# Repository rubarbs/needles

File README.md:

Needles
is a 1U Eurorack Midi Controller and Mutable Instruments Yarns Companion.

This module was designed to take full advantage of Yarn's capabilities. Most of Yarn's menu settings can be accessed and changed directly from Needles front panel, allowing for very fast and intuitive workflow.

See the guides for more info.

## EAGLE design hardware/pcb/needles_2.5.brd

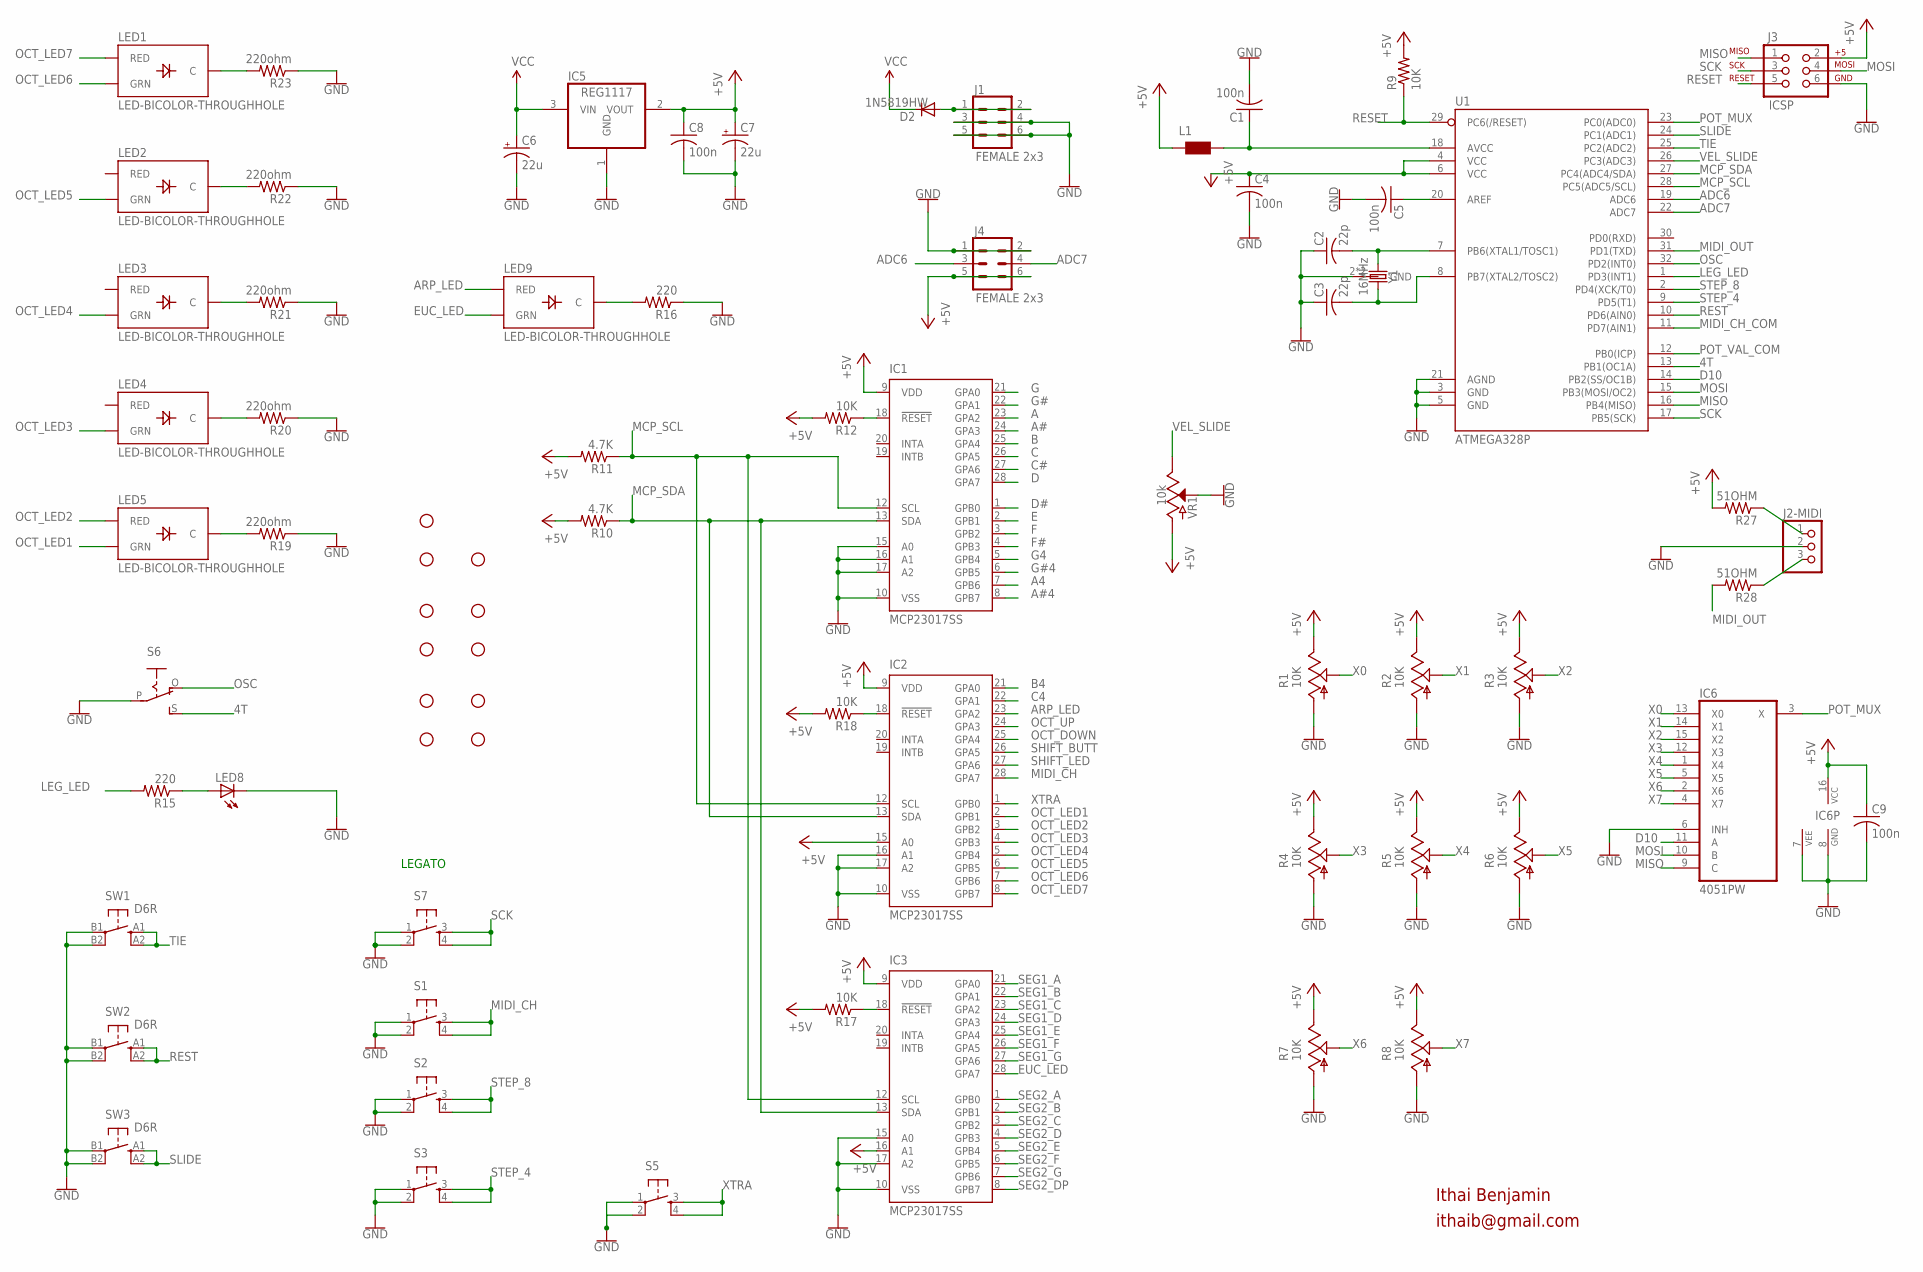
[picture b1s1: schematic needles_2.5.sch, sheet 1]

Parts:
C1, C4, C5, C8, C9: 100n; C0603
C2, C3: 22p; C0603
C6, C7: 22u; PANASONIC_C
D2: 1N5819HW; SOD123
H1, H2, H3, H4, H5, H6, H7, H8, H9, H10, H11: STAND-OFF
IC1, IC2, IC3: MCP23017SS; SSOP28
IC5: REG1117; SOT223
IC6: 4051PW; TSSOP16
J1, J4: FEMALE 2x3; 2X3
J2-MIDI: PINHD-1X3; 1X03
J3: ICSP; 2X3
L1: WE-CBF_0603; 0603
LED1, LED2, LED3, LED4, LED5, LED9: LED-BICOLOR-THROUGHHOLE
LED8: LED3MM
R1, R2, R3, R4, R5, R6, R7, R8: 10K; ALPS_POT_VERTICAL
R9, R12, R17, R18: 10K; R0603
R10, R11: 4.7K; R0603
R15, R16: 220; R0603
R19, R20, R21, R22, R23: 220ohm; R0603
R27, R28: 51OHM; R0603
S1, S2, S3, S5, S7: TAC_SWITCHPTH; TACTILE-PTH
S6: S-ON-ONSMALL_SLIDE; ES_100SP1T6B11M2QEH_SMALL
SW1, SW2, SW3: D6R
U1: ATMEGA328P; TQFP32-08
VR1: 10k; SLIDER-MEDIUM
Y1: 16MHz; CRYSTAL-SMD-5X3.2-4PAD

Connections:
4T: S6.S, U1.13 (PB1(OC1A))
+5V: C4.1, C7.+, C8.1, C9.1, IC1.9 (VDD), IC2.9 (VDD), IC2.15 (A0), IC3.9 (VDD), IC3.16 (A1), IC5.2 (VOUT), IC6.16 (VCC), J3.2, J4.5, J4.6, L1.1, R1.P$1 (E), R2.P$1 (E), R3.P$1 (E), R4.P$1 (E), R5.P$1 (E), R6.P$1 (E), R7.P$1 (E), R8.P$1 (E), R9.2, R10.2, R11.2, R12.2, R17.2, R18.2, R27.2, U1.4 (VCC), U1.6 (VCC), VR1.BOTTOM (A); also elsewhere on the board
A: IC1.23 (GPA2); also elsewhere on the board
A4: IC1.7 (GPB6); also elsewhere on the board
A#: IC1.24 (GPA3); also elsewhere on the board
A#4: IC1.8 (GPB7); also elsewhere on the board
ADC6: J4.3, U1.19 (ADC6)
ADC7: J4.4, U1.22 (ADC7)
AREF: C5.1, U1.20 (AREF)
ARP_LED: IC2.23 (GPA2), LED9.3 (RED)
B: IC1.25 (GPA4); also elsewhere on the board
B4: IC2.21 (GPA0); also elsewhere on the board
C: IC1.26 (GPA5); also elsewhere on the board
C4: IC2.22 (GPA1); also elsewhere on the board
C#: IC1.27 (GPA6); also elsewhere on the board
D: IC1.28 (GPA7); also elsewhere on the board
D10: IC6.11 (A), U1.14 (PB2(SS/OC1B))
D#: IC1.1 (GPB0); also elsewhere on the board
E: IC1.2 (GPB1); also elsewhere on the board
EUC_LED: IC3.28 (GPA7), LED9.1 (GRN)
F: IC1.3 (GPB2); also elsewhere on the board
F#: IC1.4 (GPB3); also elsewhere on the board
G: IC1.21 (GPA0); also elsewhere on the board
G4: IC1.5 (GPB4); also elsewhere on the board
G#: IC1.22 (GPA1); also elsewhere on the board
G#4: IC1.6 (GPB5); also elsewhere on the board
GND: C1.2, C2.1, C3.1, C4.2, C5.2, C6.-, C7.-, C8.2, C9.2, IC1.10 (VSS), IC1.15 (A0), IC1.16 (A1), IC1.17 (A2), IC2.10 (VSS), IC2.16 (A1), IC2.17 (A2), IC3.10 (VSS), IC3.15 (A0), IC3.17 (A2), IC5.1 (GND), IC6.6 (INH), IC6.7 (VEE), IC6.8 (GND), J1.3, J1.4, J1.5, J1.6, J2-MIDI.2, J3.6, J4.1, J4.2, LED8.K (C), R1.P$3 (A), R2.P$3 (A), R3.P$3 (A), R4.P$3 (A), R5.P$3 (A), R6.P$3 (A), R7.P$3 (A), R8.P$3 (A), R16.1, R19.1, R20.1, R21.1, R22.1, R23.1, S1.1, S1.2, S2.1, S2.2, S3.1, S3.2, S5.1, S5.2, S6.P, S7.1, S7.2, SW1.B1, SW1.B2 (P1), SW2.B1, SW2.B2 (P1), SW3.B1, SW3.B2 (P1), U1.3 (GND), U1.5 (GND), U1.21 (AGND), VR1.WIPER (S), Y1.2 (GND), Y1.4 (GND); also elsewhere on the board
LEG_LED: R15.2, U1.1 (PD3(INT1))
MCP_SCL: IC1.12 (SCL), IC2.12 (SCL), IC3.12 (SCL), R11.1, U1.28 (PC5(ADC5/SCL))
MCP_SDA: IC1.13 (SDA), IC2.13 (SDA), IC3.13 (SDA), R10.1, U1.27 (PC4(ADC4/SDA))
MIDI_CH: IC2.28 (GPA7), S1.3, S1.4
MIDI_CH_COM: U1.11 (PD7(AIN1)); also elsewhere on the board
MIDI_OUT: R28.2, U1.31 (PD1(TXD))
MISO: IC6.9 (C), J3.1, U1.16 (PB4(MISO))
MOSI: IC6.10 (B), J3.4, U1.15 (PB3(MOSI/OC2))
unnamed: IC1.18 (!RESET), R12.1
unnamed: IC2.18 (!RESET), R18.1
unnamed: C1.1, L1.2, U1.18 (AVCC)
unnamed: LED1.2 (C), R23.2
unnamed: C2.2, U1.7 (PB6(XTAL1/TOSC1)), Y1.1
unnamed: C3.2, U1.8 (PB7(XTAL2/TOSC2)), Y1.3 (2)
unnamed: LED2.2 (C), R22.2
unnamed: IC3.18 (!RESET), R17.1
unnamed: LED3.2 (C), R21.2
unnamed: LED4.2 (C), R20.2
unnamed: LED5.2 (C), R19.2
unnamed: J2-MIDI.1, R27.1
unnamed: J2-MIDI.3, R28.1
unnamed: LED8.A, R15.1
unnamed: LED9.2 (C), R16.2
unnamed: D2.A, J1.1, J1.2
OCT_DOWN: IC2.25 (GPA4); also elsewhere on the board
OCT_LED1: IC2.2 (GPB1), LED5.1 (GRN)
OCT_LED2: IC2.3 (GPB2), LED5.3 (RED)
OCT_LED3: IC2.4 (GPB3), LED4.1 (GRN)
OCT_LED4: IC2.5 (GPB4), LED3.1 (GRN)
OCT_LED5: IC2.6 (GPB5), LED2.1 (GRN)
OCT_LED6: IC2.7 (GPB6), LED1.1 (GRN)
OCT_LED7: IC2.8 (GPB7), LED1.3 (RED)
OCT_UP: IC2.24 (GPA3); also elsewhere on the board
OSC: S6.O, U1.32 (PD2(INT0))
POT_MUX: IC6.3 (X), U1.23 (PC0(ADC0))
POT_VAL_COM: U1.12 (PB0(ICP)); also elsewhere on the board
RESET: J3.5, R9.1, U1.29 (PC6(/RESET))
REST: SW2.A1 (S), SW2.A2 (S1), U1.10 (PD6(AIN0))
SCK: J3.3, S7.3, S7.4, U1.17 (PB5(SCK))
SEG1_A: IC3.21 (GPA0); also elsewhere on the board
SEG1_B: IC3.22 (GPA1); also elsewhere on the board
SEG1_C: IC3.23 (GPA2); also elsewhere on the board
SEG1_D: IC3.24 (GPA3); also elsewhere on the board
SEG1_E: IC3.25 (GPA4); also elsewhere on the board
SEG1_F: IC3.26 (GPA5); also elsewhere on the board
SEG1_G: IC3.27 (GPA6); also elsewhere on the board
SEG2_A: IC3.1 (GPB0); also elsewhere on the board
SEG2_B: IC3.2 (GPB1); also elsewhere on the board
SEG2_C: IC3.3 (GPB2); also elsewhere on the board
SEG2_D: IC3.4 (GPB3); also elsewhere on the board
SEG2_DP: IC3.8 (GPB7); also elsewhere on the board
SEG2_E: IC3.5 (GPB4); also elsewhere on the board
SEG2_F: IC3.6 (GPB5); also elsewhere on the board
SEG2_G: IC3.7 (GPB6); also elsewhere on the board
SHIFT_BUTT: IC2.26 (GPA5); also elsewhere on the board
SHIFT_LED: IC2.27 (GPA6); also elsewhere on the board
SLIDE: SW3.A1 (S), SW3.A2 (S1), U1.24 (PC1(ADC1))
STEP_4: S3.3, S3.4, U1.9 (PD5(T1))
STEP_8: S2.3, S2.4, U1.2 (PD4(XCK/T0))
TIE: SW1.A1 (S), SW1.A2 (S1), U1.25 (PC2(ADC2))
VCC: C6.+, D2.C, IC5.3 (VIN)
VEL_SLIDE: U1.26 (PC3(ADC3)), VR1.TOP (E)
X0: IC6.13 (X0), R1.P$2 (S)
X1: IC6.14 (X1), R2.P$2 (S)
X2: IC6.15 (X2), R3.P$2 (S)
X3: IC6.12 (X3), R4.P$2 (S)
X4: IC6.1 (X4), R5.P$2 (S)
X5: IC6.5 (X5), R6.P$2 (S)
X6: IC6.2 (X6), R7.P$2 (S)
X7: IC6.4 (X7), R8.P$2 (S)
XTRA: IC2.1 (GPB0), S5.3, S5.4

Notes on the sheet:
LEGATO
Ithai Benjamin
ithaib@gmail.com

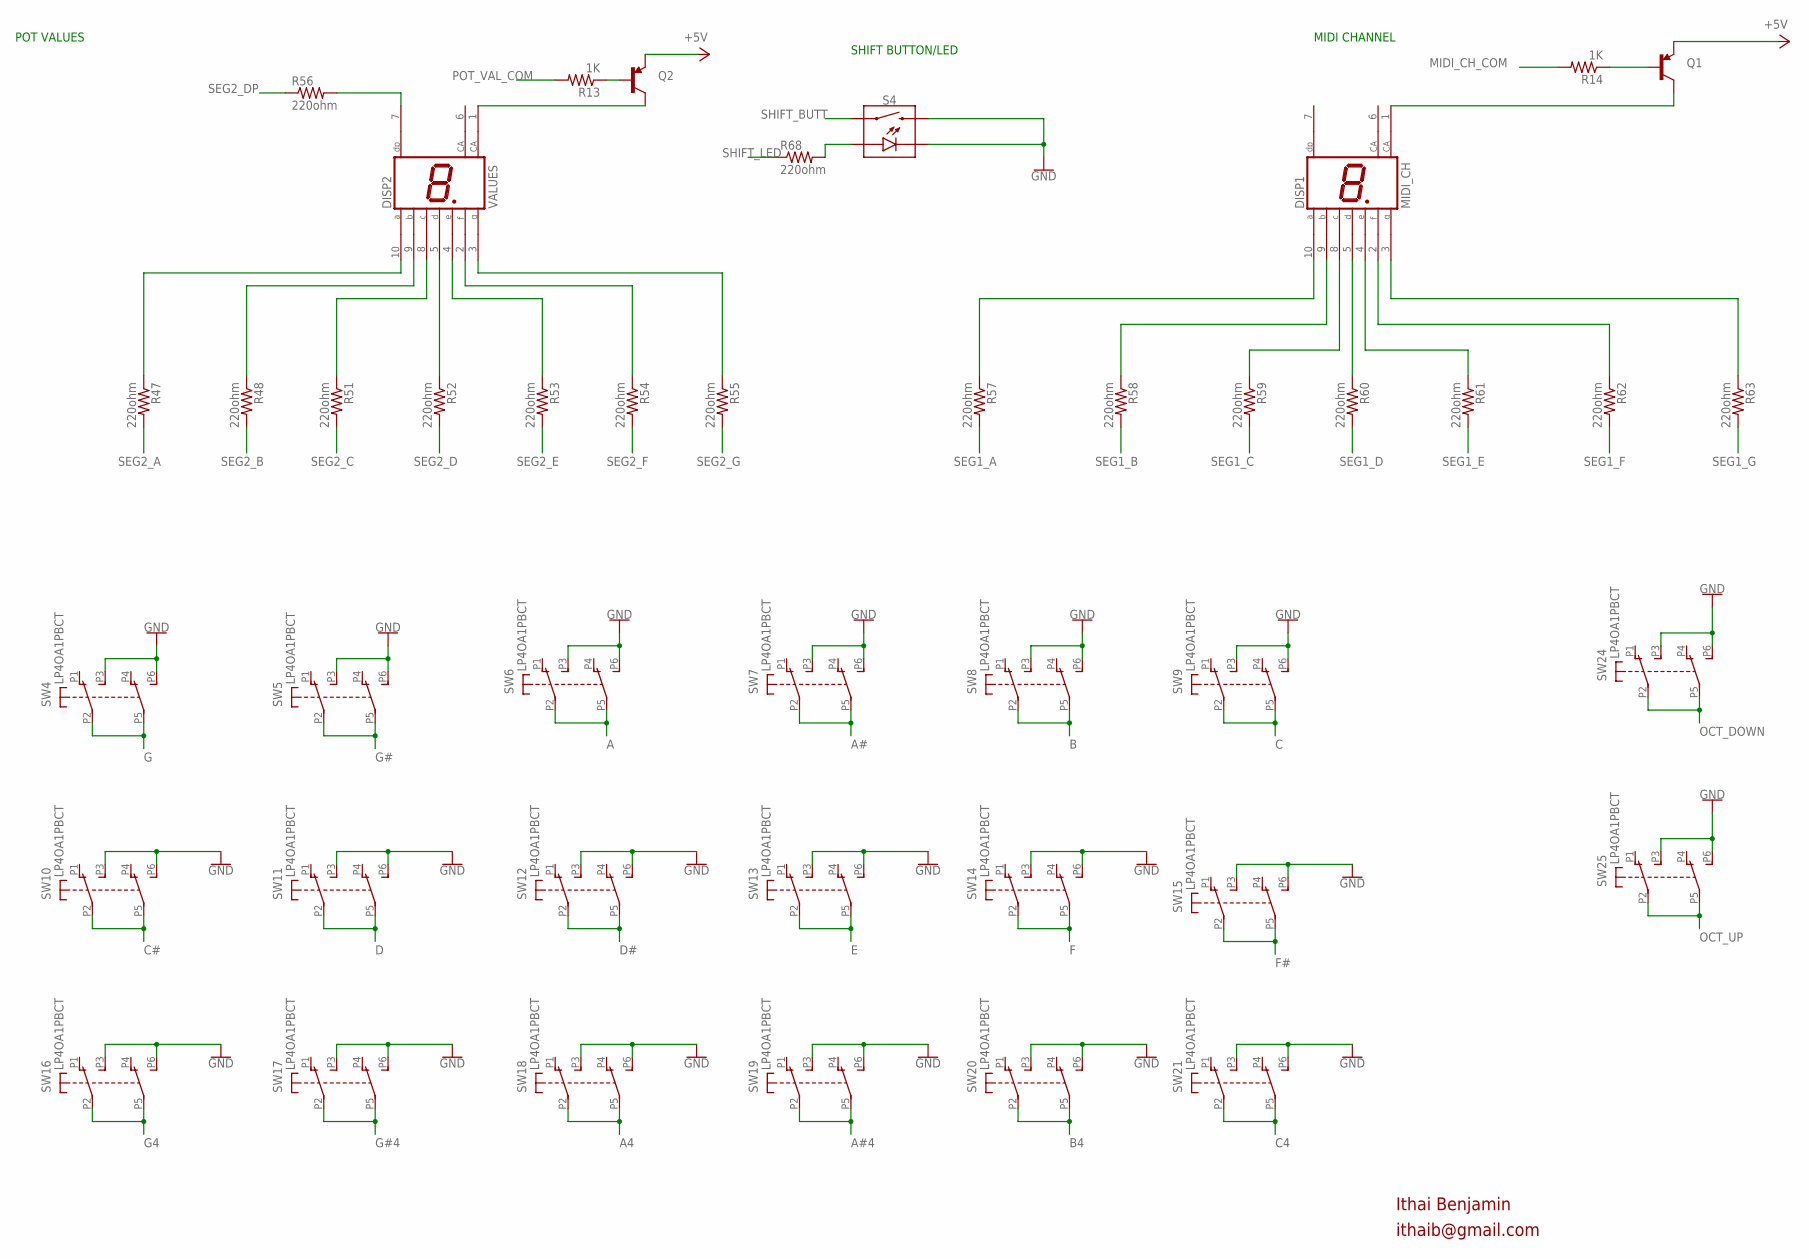
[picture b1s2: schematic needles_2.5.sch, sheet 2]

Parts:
DISP1: MIDI_CH; DISPLAY-HP_HDSP-E
DISP2: VALUES; DISPLAY-HP_HDSP-E
Q1, Q2: TRANSISTOR_PNPSMD; SOT23-3
R13, R14: 1K; R0603
R47, R48, R51, R52, R53, R54, R55, R56, R57, R58, R59, R60, R61, R62, R63, R68: 220ohm; R0603
S4: MOMENTARY-SWITCH-SPST-LED-PTH-12MM; TACTILE_SWITCH_LED_PTH_12MM
SW4, SW5, SW6, SW7, SW8, SW9, SW10, SW11, SW12, SW13, SW14, SW15, SW16, SW17, SW18, SW19, SW20, SW21, SW24, SW25: LP4OA1PBCT

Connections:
+5V: Q1.2 (E), Q2.2 (E); also elsewhere on the board
A: SW6.P2 (A2), SW6.P5 (B2); also elsewhere on the board
A4: SW18.P2 (A2), SW18.P5 (B2); also elsewhere on the board
A#: SW7.P2 (A2), SW7.P5 (B2); also elsewhere on the board
A#4: SW19.P2 (A2), SW19.P5 (B2); also elsewhere on the board
B: SW8.P2 (A2), SW8.P5 (B2); also elsewhere on the board
B4: SW20.P2 (A2), SW20.P5 (B2); also elsewhere on the board
C: SW9.P2 (A2), SW9.P5 (B2); also elsewhere on the board
C4: SW21.P2 (A2), SW21.P5 (B2); also elsewhere on the board
C#: SW10.P2 (A2), SW10.P5 (B2); also elsewhere on the board
D: SW11.P2 (A2), SW11.P5 (B2); also elsewhere on the board
D#: SW12.P2 (A2), SW12.P5 (B2); also elsewhere on the board
E: SW13.P2 (A2), SW13.P5 (B2); also elsewhere on the board
F: SW14.P2 (A2), SW14.P5 (B2); also elsewhere on the board
F#: SW15.P2 (A2), SW15.P5 (B2); also elsewhere on the board
G: SW4.P2 (A2), SW4.P5 (B2); also elsewhere on the board
G4: SW16.P2 (A2), SW16.P5 (B2); also elsewhere on the board
G#: SW5.P2 (A2), SW5.P5 (B2); also elsewhere on the board
G#4: SW17.P2 (A2), SW17.P5 (B2); also elsewhere on the board
GND: S4.1 (2), S4.2, S4.C, SW4.P3 (A3), SW4.P6 (B3), SW5.P3 (A3), SW5.P6 (B3), SW6.P3 (A3), SW6.P6 (B3), SW7.P3 (A3), SW7.P6 (B3), SW8.P3 (A3), SW8.P6 (B3), SW9.P3 (A3), SW9.P6 (B3), SW10.P3 (A3), SW10.P6 (B3), SW11.P3 (A3), SW11.P6 (B3), SW12.P3 (A3), SW12.P6 (B3), SW13.P3 (A3), SW13.P6 (B3), SW14.P3 (A3), SW14.P6 (B3), SW15.P3 (A3), SW15.P6 (B3), SW16.P3 (A3), SW16.P6 (B3), SW17.P3 (A3), SW17.P6 (B3), SW18.P3 (A3), SW18.P6 (B3), SW19.P3 (A3), SW19.P6 (B3), SW20.P3 (A3), SW20.P6 (B3), SW21.P3 (A3), SW21.P6 (B3), SW24.P3 (A3), SW24.P6 (B3), SW25.P3 (A3), SW25.P6 (B3); also elsewhere on the board
MIDI_CH_COM: R14.2; also elsewhere on the board
unnamed: R68.2, S4.A
unnamed: Q1.1 (B), R14.1
unnamed: Q2.1 (B), R13.1
unnamed: DISP2.1 (CA), Q2.3 (C)
unnamed: DISP2.10 (A), R47.1
unnamed: DISP2.9 (B), R48.1
unnamed: DISP2.8 (C), R51.1
unnamed: DISP2.5 (D), R52.1
unnamed: DISP2.4 (E), R53.1
unnamed: DISP2.2 (F), R54.1
unnamed: DISP2.3 (G), R55.1
unnamed: DISP1.10 (A), R57.1
unnamed: DISP2.7 (DP), R56.2
unnamed: DISP1.1 (CA), Q1.3 (C)
unnamed: DISP1.9 (B), R58.1
unnamed: DISP1.8 (C), R59.1
unnamed: DISP1.5 (D), R60.1
unnamed: DISP1.4 (E), R61.1
unnamed: DISP1.2 (F), R62.1
unnamed: DISP1.3 (G), R63.1
OCT_DOWN: SW24.P2 (A2), SW24.P5 (B2); also elsewhere on the board
OCT_UP: SW25.P2 (A2), SW25.P5 (B2); also elsewhere on the board
POT_VAL_COM: R13.2; also elsewhere on the board
SEG1_A: R57.2; also elsewhere on the board
SEG1_B: R58.2; also elsewhere on the board
SEG1_C: R59.2; also elsewhere on the board
SEG1_D: R60.2; also elsewhere on the board
SEG1_E: R61.2; also elsewhere on the board
SEG1_F: R62.2; also elsewhere on the board
SEG1_G: R63.2; also elsewhere on the board
SEG2_A: R47.2; also elsewhere on the board
SEG2_B: R48.2; also elsewhere on the board
SEG2_C: R51.2; also elsewhere on the board
SEG2_D: R52.2; also elsewhere on the board
SEG2_DP: R56.1; also elsewhere on the board
SEG2_E: R53.2; also elsewhere on the board
SEG2_F: R54.2; also elsewhere on the board
SEG2_G: R55.2; also elsewhere on the board
SHIFT_BUTT: S4.3 (1), S4.4 (1); also elsewhere on the board
SHIFT_LED: R68.1; also elsewhere on the board

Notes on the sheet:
MIDI CHANNEL
POT VALUES
SHIFT BUTTON/LED
Ithai Benjamin
ithaib@gmail.com

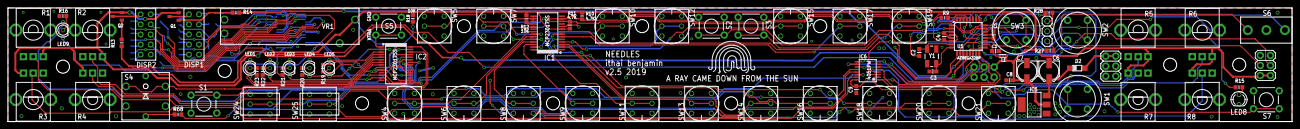
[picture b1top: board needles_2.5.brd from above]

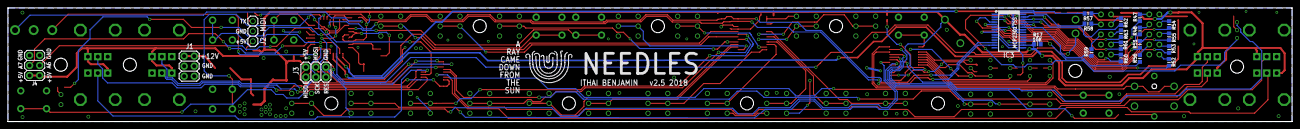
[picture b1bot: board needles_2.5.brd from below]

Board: 2 copper layers, 324.4 x 28.7 mm, 116 parts (18 on the bottom side), 118 nets.

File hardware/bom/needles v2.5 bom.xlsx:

NEEDLES v2.5 - BOM
Mouser Cart: https://www.mouser.com/ProjectManager/ProjectDetail.aspx?AccessID=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
Parts | Qty | Description | Value | Package | MOUSER PART #
RESISTORS / CAPS
R27, R28 | 2.0 | RESISTOR, 1% | 51 Ohm | 0603 | 652-CR0603FX-51R0ELF
R13, R14 | 2.0 | RESISTOR, 1% | 1K | 0603 | 652-CR0603FX-1001ELF
R9, R12, R17, R18 | 4.0 | RESISTOR, 1% | 10K | 0603 | 652-CR0603FX-1002ELF OR 667-ERJ-3EKF1002V
R10, R11 | 2.0 | RESISTOR, 1% | 4.7K | 0603 | 652-CR0603FX-4701ELF
R15, R16, R19, R20, R21, R22, R23, R47, R48, R51, R52, R53, R54, R55, R56, R57,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 | 23.0 | RESISTOR, 1% | 220 Ohm | 0603 | 652-CR0603FX-2200ELF
C2, C3 | 2.0 | CAPACITOR, ceramic | 22pf | 0603 | 81-GRM185C1H220JA01J or 80-C0603C220J5G7411
C1, C4, C5, C8, C9 | 5.0 | CAPACITOR, ceramic | 100n | 0603 | 81-GRM188R61C104KA1D
C6, C7 | 2.0 | CAPACITOR, electrolytic | 22u | PANASONIC C | 667-EEE-FP1E220AR
ICS / OTHER
L1 | 1.0 | Ferrite Bead |  | 0603 | 710-742792642
D2 | 1.0 | 1N5819HW diode | 1N5819HW | SOD123 | 621-1N5819HW-F
IC1, IC2, IC3 | 3.0 | MCP23017-E/SS I/O expander | MCP23017SS | SSOP28 | 579-MCP23017-E/SS
IC5 | 1.0 | LM1117-3.3V LDO Vreg | REG1117 | SOT223 | 926-LM1117MPX3.3NOPB
IC6 | 1.0 | CD4051 8-1 multiplexer | 4051PW | TSSOP16 | 595-CD4051BPWR
Y1 | 1.0 | 16MHz Crystal | 16MHz | CRYSTAL-SMD-5X3.2-4PAD | 815-ABM3B-16-B2
U1 | 1.0 | ATMega328p | ATMEGA328P | TQFP32-08 | 556-ATMEGA328P-AU
Q1, Q2 | 2.0 | 2n3906 Transistor | MMBT3906LT1G | MMBT3906LT1G | 863-MMBT3906LT1G
SWITCHES / BUTTONS
SW1 | 1.0 | Push-button, Yellow | Rest | C&K - Yellow | 611-D6R30F1LFS
SW2 | 1.0 | Push-button, Blue | Tie | C&K - Blue | 611-D6R60F1LFS
SW3 | 1.0 | Push-button, Green | Slide | C&K - Green | 611-D6R50F1LFS
SW4, SW5, SW6, SW7, SW8, SW9, SW10, SW11, SW12, SW13, SW14, SW15, SW16, SW17, S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 | 20.0 | Push-button | 18 Keyboard 2 Octave | E-switch TL2201OAYA | 612-TL2201
SW Caps - Keyboard - 11 white / 7 Gray | 18.0 | Cap Round - 3.3mm shaft size | Keyboard caps | C&K | black 611-21125, white 611-F0202, gray 611-F0204
SW Caps - Octave - 2 red | 2.0 | Cap Rectangle - 3.3mm shaft size | octave | C&K | 611-F1203 (OR Selco PB 07/50/000)
S1, S2, S3, S7 | 5.0 | Tact Switch, 6mm | midi, legato, 3, 7, xtra | E-Switch - TL1105SPF160Q | 612-TL1105SP
Tact Switch Caps | 5.0 | Tact Caps 2.8mm shaft size | midi, legato, 3, 7, xtra |  | SELCO PB 10/51/000 - these are longer
S4 | 1.0 | Pushbutton - SPST - w/ LED | Shift | E-Switch - LP15S1WHTRED-N | 612-LP15S1WHTRED-N
S6 | 1.0 | Toggle switch, on-off-on | OSC-DEF-4T | C&K | 5mm actuator: 611-1103M2S3CQE2 12mm actuator: 611-1103M2S6CBE2 or NKK 633-M2013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
LED
LED1, LED2, LED3, LED4, LED5, LED9 | 6.0 | LED 3mm, Red/Green, 3 terminals | Octave, arp |  | 604-WP115VEGW
LED8 | 1.0 | LED 3mm, 2 terminals | Legato |  | Red - 604-WP710A10ID, Green - 604-WP710A10GD
DISP1 | 1.0 | 7 Segment Display Green | Values |  | 755-LA-401MD OR 630-HDSP-F501
DISP2 | 1.0 | 7 Segment Display Red | Midi Channel |  | 755-LA-401VD OR 630-HDSP-F151
POTENTIOMETERS
R1, R2, R3, R4, R5, R6, R7, R8 | 8.0 | 10k linear pot, 25mm shaft with marker | 10K |  | Erthenvar , Thonk
VR1 | 1.0 | Slide Potentiometer | 10k |  | 652-PTA20432015CPB10
Slider cap | 1.0 | Slider Cap | optional |  | White - 633-AT4003B / Red - 633-AT4003C / Yellow - 633-AT434E
VARIOUS
J1, J3 | 2.0 | 2x3 Male Header 2.54mm | Power and ICSP | Amphenol/FCI | 649-67996-172HLF (this one is 2x36)
JP2 | 1.0 | 1x3 Male Header 2.54mm | MIDI |  | 649-77311-118-03LF (3 pin) 649-77311-118-24LF (24 pin)
Female Headers | 2.0 | 12x5 Female SMD Header | For displays |  | 517-9662102000ARPR
Servo cable | 1.0 | Female to Male | MIDI out —> Yarns MIDI In | Adafruit | 485-972
H1, H2, H3, H4, H5, H6, H7, H8, H9, H10 | 9.0 | Hex Stand Off 12mm x 5mm |  | Harwin | 4-40: 855-R44-1001202 M2.5: 855-R25-1001202
Screws for Stand offs | 18.0 | Flat Head screws |  | Mcmaster | 4-40: https://www.mcmaster.com/#96640A054 M2.5: https://www.mcmaster.com/91698a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

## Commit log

2019-02-23 Create hardware
2019-02-24 Create software to do list
2019-02-24 Update software to do list
2020-04-05 Rename needles_v2.4_2_test.ino to needles_v2.4_2.ino

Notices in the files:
parts and their libraries:
SparkFun-IC-Microcontroller: Licensing: Creative Commons ShareAlike 4.0 International - https://creativecommons.org/licenses/by-sa/4.0
